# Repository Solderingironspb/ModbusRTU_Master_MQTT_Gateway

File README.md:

# ModbusRTU_Master_MQTT_Gateway
Данное устройство выступает мастером сети ModbusRTU. Обменивается данными с подчиненными устройствами (до 247 устройств на линии RS485). Все данные дублируются по MQTT на сервер, где они могут обрабатываться, а также появится возможность с сервера управлять подчиненными устройствами. (При условии, что ты это все в силах сам запрограммировать, мой друг...).

### Описание:
Общение осуществляется по RS485. Согласно документации, длина линии может доходить до 1 км, а изоляция по RS485 достигает 3000 В. На этой линии могут находиться счетчики электрической энергии, промышленные холодильники, климатические камеры, кондиционеры, щиты управления чего-либо и много чего другого. ModbusRTU используется с 1979 года по сей день и промышленных устройств, поддерживающих этот протокол миллионы.

### Немного по технической части:
Основную задачу по работе с ModbusRTU берет на себя RISC-V микроконтроллер CH32V203F8P6. На нем заданы тайминги для правильной работы протокола и написана своя реализация ModbusRTU Master. Все написано на RVMSIS. Отличный, очень компактный камушек с двумя UART на борту. Единственный минус данного МК - он не имеет входа кварцевого резонатора, поэтому сильно задирать скорость UART не стал бы. Обычного 9600 - 115200 хватит. Пока тестирую на 9600. Работает без сбоев.
По части WIFI - здесь распаян WiFi модуль на базе однокристальной системы (SoC) ESP8266. Написано свое ПО для модуля, что оно работает в качестве WIFI MQTT шлюза. Общение с CH32V203F8P6 происходит через USART по самописному протоколу, которым я пользуюсь уже 3 года без сбоев.
Многие, кто в теме задаст очередной вопрос, почему всю работу не осуществить на ESP8266? Отвечаю: я не знаю на столько хорошо ES8266, чтоб доверить ей работу с прерываниями, таймерами и прочим. Система, по которой я работаю - обкатана годами. Менять пока не собираюсь.

### По корпусу:
Очень хотелось выпендриться и уместить все в корпус на DIN рейку и чтоб 1 модуль занимало всего лишь. Из за этого мы видим антенну, которая немного мешает подключать RS485 (GND), но опять же....как часто мы GND туда подцепляем?) На 80% устройств она отсутствует в принципе.
DCDC преобразователем, чтоб можно было питать устройство от 12-24В тоже пришлось пожертвовать, негде его там расположить внутри). Поэтому питание устройства от 5В. Защита от переполюсовки присутствует.
Не знал, как поступить с портом для программирования устройства. На лицевую сторону тяжело уже было вывести, поэтому ничего не оставалось, как сделать окошко в корпусе справа. Открыл - запрогал - закрыл.

### По дизайну:
Все в традициях нашего оборудования) Немного уродливо, зато с душой и относительно бюджетно 😁

### Ну и не забываем, что все делалось в домашних условиях)

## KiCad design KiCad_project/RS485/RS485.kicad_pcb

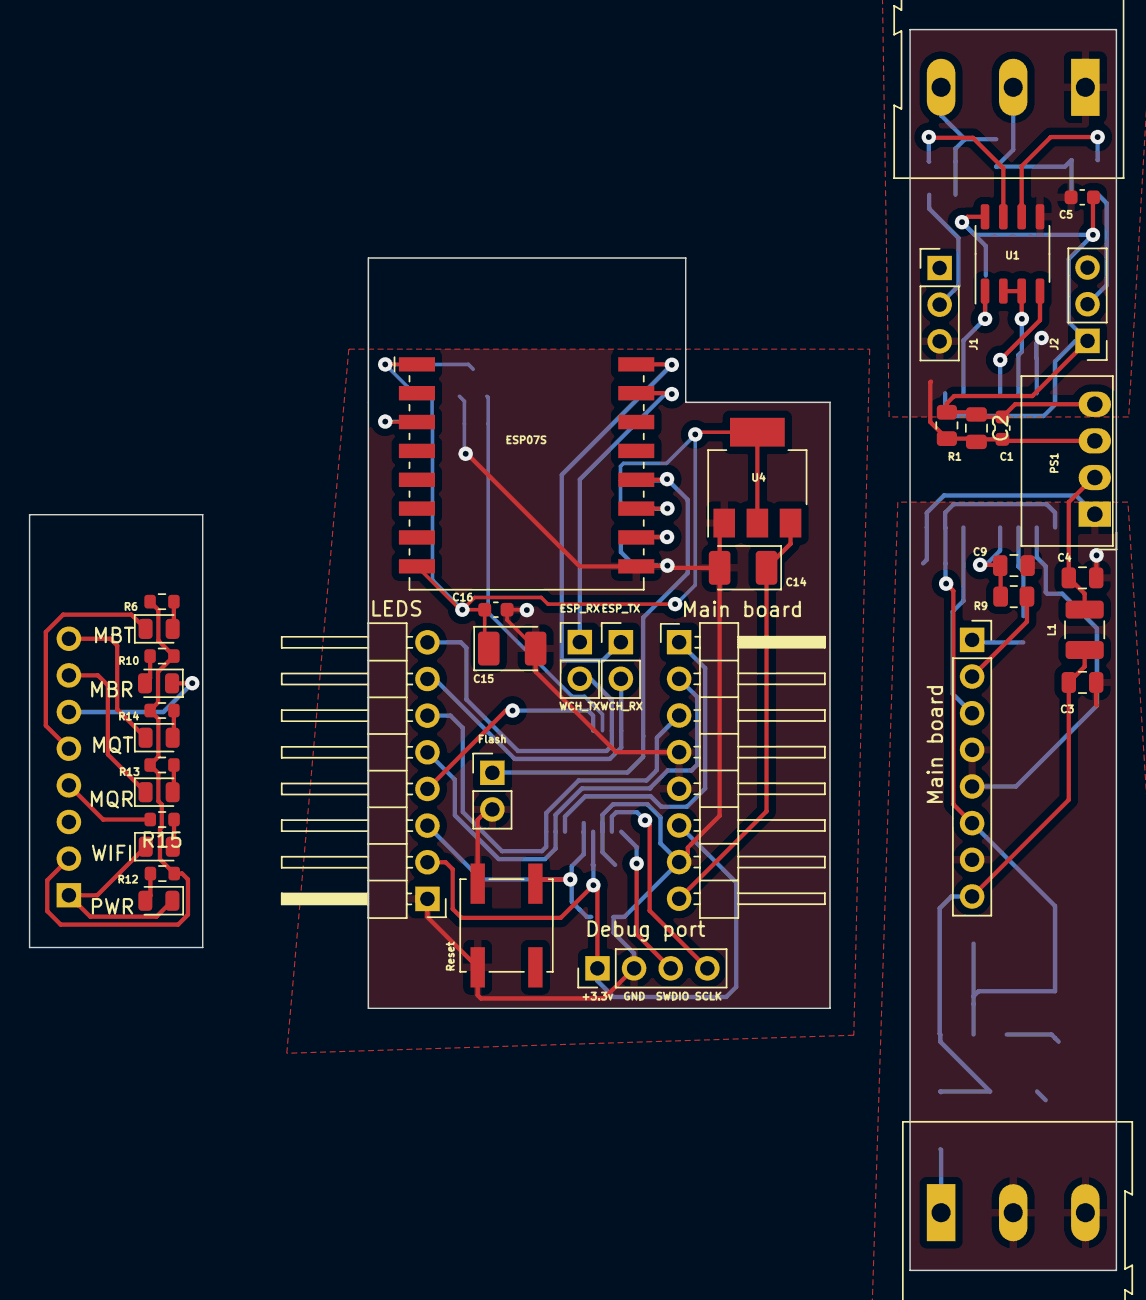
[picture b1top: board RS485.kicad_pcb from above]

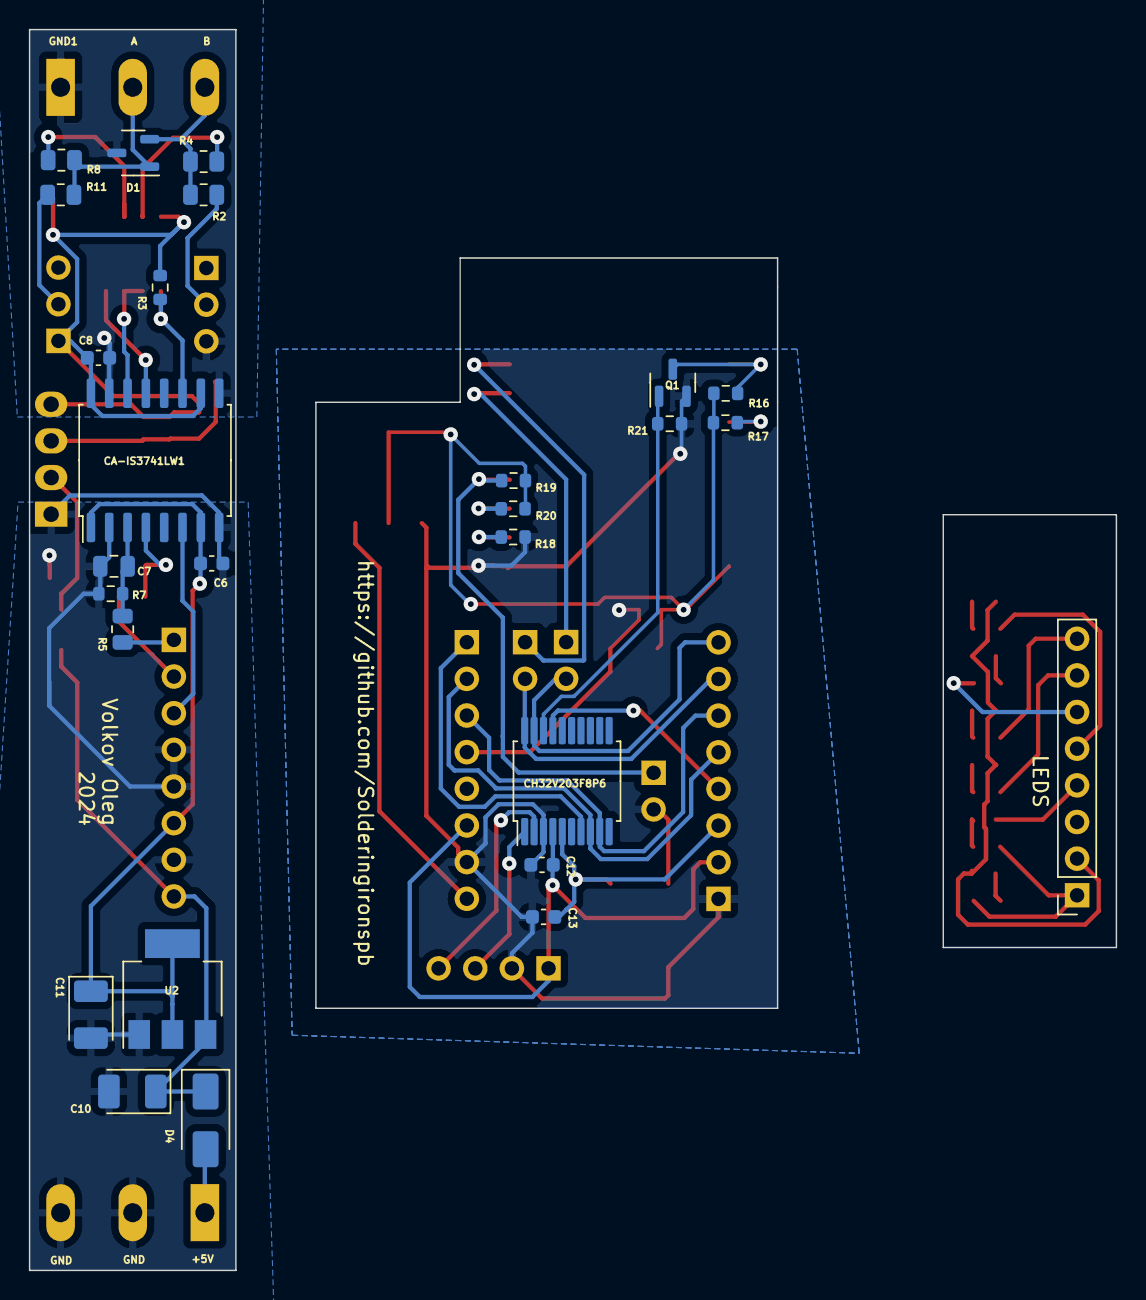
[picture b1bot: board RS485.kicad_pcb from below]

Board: 2 copper layers, 75.3 x 86.0 mm, 65 parts (27 on the bottom side), 41 nets.

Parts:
C1, C5, C6, C8: 100n; C_0603_1608Metric
C2: 10uF; C_0805_2012Metric
C3, C4: 5uF; C_0805_2012Metric
C7, C9: 220pF; C_0805_2012Metric
C10, C11, C14, C15: 47uF; CP_EIA-3528-21_Kemet-B_Pad1.50x2.35mm_HandSolder
C12, C13, C16: 100nF; C_0603_1608Metric
CA-IS3741LW1: SOIC-16W_7.5x10.3mm_P1.27mm
CH32V203F8P6: SSOP-20_5.3x7.2mm_P0.65mm
D1: PSM712-LF-T7; SOT-23-3
D4: 10MQ100NPBF; D_SMA
Debug port: Debug; PinHeader_1x04_P2.54mm_Vertical
ESP07S: ESP-07
ESP_RX: PinHeader_1x02_P2.54mm_Vertical
ESP_TX: PinHeader_1x02_P2.54mm_Vertical
Flash: PinHeader_1x02_P2.54mm_Vertical
J1, J2: Master/Slave; PinHeader_1x03_P2.54mm_Vertical
L1: 22uH; L_1210_3225Metric
LEDS: PinHeader_1x08_P2.54mm_Horizontal
LEDS#2: PinSocket_1x08_P2.54mm_Vertical
MBR: Rx2; D_0805_2012Metric
MBT: Tx2; D_0805_2012Metric
MQR: Rx1; D_0805_2012Metric
MQT: Tx1; D_0805_2012Metric
Main board: PinHeader_1x08_P2.54mm_Horizontal
Main board#2: PinSocket_1x08_P2.54mm_Vertical
PS1: MornsunS0505SC; Converter_DCDC_Murata_MEE1SxxxxSC_THT
PWR: LED; D_0805_2012Metric
Q1: IRLML0060; SOT-23
R1: 240; R_0805_2012Metric
R2, R11: 470R; R_0805_2012Metric
R3, R7, R16, R17, R18, R19, R20, R21: 10k; R_0603_1608Metric
R4, R8: 10R; R_0805_2012Metric
R5, R9: 100R; R_0805_2012Metric
R6, R10, R12, R13, R14, R15: 1k; R_0603_1608Metric
Reset: Reset; SW_Push_1P1T_NO_CK_KSC6xxJ
U1: MAX485E; SO-8_3.9x4.9mm_P1.27mm
U2, U4: AMS1117-3.3; SOT-223-3_TabPin2
WIFI: Rx1; D_0805_2012Metric

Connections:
+3.3V: C15.1, C16.1, ESP07S.8 (VCC), R16.1, R17.1, R19.1, R20.1, U4.2 (VO)
+3V3: C6.1, C11.1, C12.1, CA-IS3741LW1.1 (VDDA), CA-IS3741LW1.7 (ENA), CH32V203F8P6.4 (VDD), Debug port.1, LEDS.2, LEDS#2.2, Main board.6, Main board#2.6, R6.1, R10.1, R12.1, R13.2, R14.2, U2.2 (VO)
+5V: C3.1, C10.1, C14.1, D4.1 (K), L1.1, Main board.8, Main board#2.8, U2.3 (VI), U4.3 (VI)
A: D1.1 (A1), R8.2, R11.1
B: D1.2 (A2), R2.2, R4.2
ESP_UART_Rx: ESP07S.15 (GPIO3/RXD), ESP_RX.1
ESP_UART_Tx: ESP07S.16 (GPIO1/TXD), ESP_TX.1
GND: C3.2, C4.2, C6.2, C7.2, C9.2, C10.2, C11.2, C12.2, C13.2, C14.2, C15.2, C16.2, CA-IS3741LW1.2 (GNDA), CA-IS3741LW1.8 (GNDA), CH32V203F8P6.3 (VSS), Debug port.2, ESP07S.9 (GND), Flash.2, LEDS.1, LEDS#2.1, Main board.4, Main board.5, Main board.7, Main board#2.4, Main board#2.5, Main board#2.7, PS1.1 (-Vin), PWR.1 (K), Q1.2 (S), R7.2, R18.2, R21.2, Reset.1 (A), U2.1 (GND), U4.1 (GND), WIFI.1 (K)
GND1: C1.2, C2.2, C5.2, C8.2, CA-IS3741LW1.9 (GNDB), CA-IS3741LW1.15 (GNDB), D1.3 (common), J1.3, PS1.3 (-Vout), R1.2, U1.5 (GND)
unnamed: C7.1, CA-IS3741LW1.3 (VI1), R5.2, R7.1
unnamed: C9.1, CA-IS3741LW1.4 (VI2), R9.2
unnamed: CA-IS3741LW1.11 (VI4), R3.2, U1.1 (RO)
unnamed: CA-IS3741LW1.14 (VO1), U1.2 (~RE), U1.3 (DE)
unnamed: CA-IS3741LW1.13 (VO2), U1.4 (DI)
unnamed: C13.1, CH32V203F8P6.5 (NRST), LEDS.3, LEDS#2.3, Reset.2 (A)
unnamed: CH32V203F8P6.17 (PB15), LEDS.4, LEDS#2.4, R15.2
unnamed: MBT.2 (A), R6.2
unnamed: MBR.2 (A), R10.2
unnamed: PWR.2 (A), R12.2
unnamed: MQR.2 (A), R13.1
unnamed: MQT.2 (A), R14.1
unnamed: R15.1, WIFI.2 (A)
unnamed: J1.2, R2.1
unnamed: J2.2, R11.2
unnamed: C4.1, L1.2, PS1.2 (+Vin)
unnamed: ESP07S.1 (~RST), Q1.3 (D), R16.2
unnamed: R8.1, U1.6 (A)
unnamed: R4.1, U1.7 (B)
unnamed: ESP07S.3 (EN), R17.2
unnamed: ESP07S.12 (GPIO0), Flash.1, R19.2
unnamed: ESP07S.11 (GPIO2), R20.2
unnamed: ESP07S.10 (GPIO15), R18.1
PA8: CH32V203F8P6.18 (PA8), Q1.1 (G), R21.1
PA9: CH32V203F8P6.19 (PA9), ESP_RX.2, LEDS.8, LEDS#2.8, MQT.1 (K)
PA10: CH32V203F8P6.20 (PA10), ESP_TX.2, LEDS.7, LEDS#2.7, MQR.1 (K)
RO/DI: CH32V203F8P6.7 (PA1), Main board.1, Main board#2.1, R5.1
Rx: CA-IS3741LW1.6 (VO4), CH32V203F8P6.9 (PA3), LEDS.6, LEDS#2.6, MBR.1 (K), Main board.3, Main board#2.3
SCLK: CH32V203F8P6.2 (PB7), Debug port.4
SWDIO: CH32V203F8P6.1 (PB6), Debug port.3
Tx: CH32V203F8P6.8 (PA2), LEDS.5, LEDS#2.5, MBT.1 (K), Main board.2, Main board#2.2, R9.1
VDDB: C1.1, C2.1, C5.1, C8.1, CA-IS3741LW1.10 (ENB), CA-IS3741LW1.16 (VDDB), J2.1, PS1.4 (+Vout), R1.1, R3.1, U1.8 (VCC)

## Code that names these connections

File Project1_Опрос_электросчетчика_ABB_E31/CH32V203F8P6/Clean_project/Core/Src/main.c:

/* CH32V203F8P6 ModbusRTU Master
 * ESP8266 UART to MQTT transmitter
 * Debug:
 * PB6 - SWDIO
 * PB7 - SWCLK
 * USART2 - ModbusRTU(RS485):
 * PA1 - RO/DI
 * PA2 - Tx2
 * PA3 - Rx2
 * USART1 - ESP8266
 * PA9 - Tx1
 * PA10 -Rx1
 * */

#include "main.h"
#include "stdio.h"
#include <stdbool.h>
#include "ESP8266_lib.h"
#include "MQTT.h"
#include "SoftwareTimer.h"

extern struct USART_name husart1; //Объявляем структуру по USART.(см. ch32v203x_RVMSIS.h)
extern uint8_t NETWORK_Status;
uint8_t MQTT_Arr[64] = { 0, };

extern float ABB_E31_Total_active_energy;       //01
extern float ABB_E31_Active_energy_1;           //02
extern float ABB_E31_Active_energy_2;           //03
extern float ABB_E31_Active_energy_3;           //04
extern float ABB_E31_Active_energy_4;           //05
extern float ABB_E31_Voltage;                      //06
extern float ABB_E31_Amp;                          //07
extern float ABB_E31_Active_power;                 //08
extern float ABB_E31_Power_factor;                 //09
extern float ABB_E31_Frequency;                    //10
extern int16_t ABB_E31_Temperature;                //11

extern bool flags_tx_data_ready[64];
//extern bool flags_read_data_block[64];

/*====================================Добавить в main.c====================================*/
uint32_t ModbusRTU_Timeout = 0; //Таймаут для ответов
uint32_t ModbusRTU_delay_between_pool = 0; //Задержка между фреймами
volatile uint8_t ModbusRTU_Counter_in_queue = 0; //Счетчик запросов в отчереди на отправку слейв устройствам. Номер счетчика соответствует отправленному запросу.
bool flag_ModbusRTU_request_on = true; //флаг, разрешающий отправку пакета
bool flag_ModbusRTU_block = false; //флаг, блокирующий работу мастера, пока не обработается входящее сообщение
/*====================================Добавить в main.c====================================*/

bool Task1 = false;
uint32_t MQTT_Send_Timer; //Таймер для отправки MQTT

void Task1_MQTT_Send(void) {
    if (NETWORK_Status == MQTT_STATUS_CONNECTED) {
        if (flags_tx_data_ready[0]) {
            UART_MQTT_Send_data_float(1, ABB_E31_Total_active_energy, MQTT_Arr);
            UART_MQTT_Send_data_float(2, ABB_E31_Active_energy_1, MQTT_Arr);
            UART_MQTT_Send_data_float(3, ABB_E31_Active_energy_2, MQTT_Arr);
            UART_MQTT_Send_data_float(4, ABB_E31_Active_energy_3, MQTT_Arr);
            UART_MQTT_Send_data_float(5, ABB_E31_Active_energy_4, MQTT_Arr);
            UART_MQTT_Send_data_float(6, ABB_E31_Voltage, MQTT_Arr);
            UART_MQTT_Send_data_float(7, ABB_E31_Amp, MQTT_Arr);
            UART_MQTT_Send_data_float(8, ABB_E31_Active_power, MQTT_Arr);
            UART_MQTT_Send_data_float(9, ABB_E31_Power_factor, MQTT_Arr);
            UART_MQTT_Send_data_float(10, ABB_E31_Frequency, MQTT_Arr);
            flags_tx_data_ready[0] = false;
        }
        if (flags_tx_data_ready[1]){
            UART_MQTT_Send_data_int16_t(11, ABB_E31_Temperature, MQTT_Arr);
            flags_tx_data_ready[1] = false;
        }
    }
}

void MQTT_Reveieve(void) {
    switch (husart1.rx_buffer[1]) {
//    case 18:
//        OWEN_PR200_Out3 = UART_MQTT_Receive_data_int16_t(husart1.rx_buffer);
//        flags_read_data_block[4] = true;
//        break;
//    case 19:
//        OWEN_PR200_Out4 = UART_MQTT_Receive_data_int16_t(husart1.rx_buffer);
//        flags_read_data_block[5] = true;
//        break;
    }
}

int main(void) {
    RVMSIS_Debug_init(); //Настройка дебага
    RVMSIS_RCC_SystemClock_144MHz(); //Настройка системной частоты.
    RVMSIS_SysTick_Timer_init(); //Настройка системного таймера на 1000 Гц.
    RVMSIS_USART2_Init(); //Настройка USART2 ModbusRTU 9600 8N1
    RVMSIS_USART1_Init(); //Настройка USART1 9600 8N1
    RVMSIS_GPIO_init(GPIOA, 1, GPIO_GENERAL_PURPOSE_OUTPUT, GPIO_OUTPUT_PUSH_PULL, GPIO_Speed_50MHz); //Настройка ножки RO/DI
    MODBUSRTU_RECEIEVE;
    RVMSIS_GPIO_init(GPIOA, 8, GPIO_GENERAL_PURPOSE_OUTPUT, GPIO_OUTPUT_PUSH_PULL, GPIO_Speed_50MHz); //ножка RESET ESP8266
    RVMSIS_GPIO_init(GPIOB, 15, GPIO_GENERAL_PURPOSE_OUTPUT, GPIO_OUTPUT_PUSH_PULL, GPIO_Speed_50MHz); //Wifi status
    RVMSIS_TIM3_init();
    ESP8266_Reset(200);

    Delay_ms(5); //Перед началой основного цикла сделаем задержку, чтоб не лез всякий мусор.

    while(1) {

        /*Выполнение работы ModbusRTU*/
        ModbusRTU_Master_pool_run();
        /*Выполнение работы ModbusRTU*/

        /*Работа индикации подключения к WIFI и MQTT*/
        ESP8266_Indication_run();
        /*Работа индикации подключения к WIFI и MQTT*/

        /*Отправка данных по MQTT*/
        if (Task1) {
            Task1_MQTT_Send();
            Task1 = false;
            Software_timer((uint32_t*) &MQTT_Send_Timer, 2000);
        }
        /*Отправка данных по MQTT*/

    }
}

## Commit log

2024-02-27 Добавил плату в KiCad + 1 пример опроса счетчика электрической энергии ABB E31
